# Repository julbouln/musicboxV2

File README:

New "La boîte à musique" firmware https://hackaday.io/project/6391-la-bote-musique

Using libopencm3 http://libopencm3.org/wiki/Main_Page drivers and atomthreads RTOS http://atomthreads.com/

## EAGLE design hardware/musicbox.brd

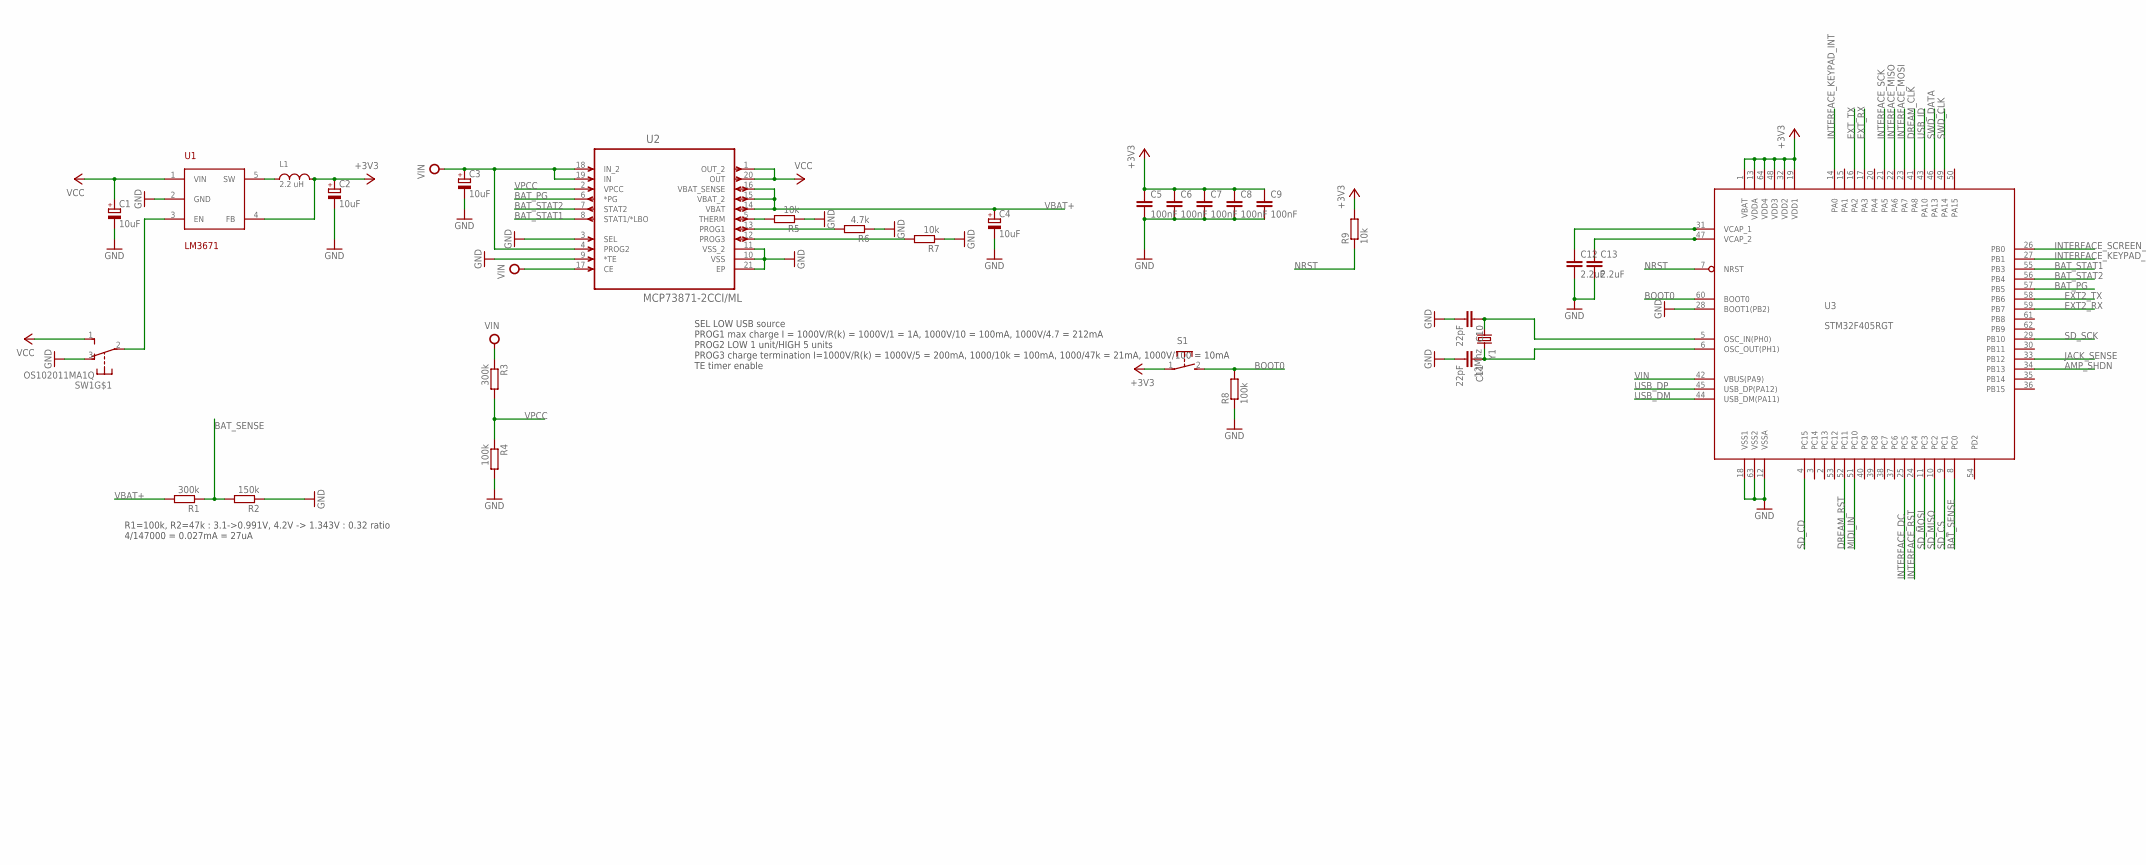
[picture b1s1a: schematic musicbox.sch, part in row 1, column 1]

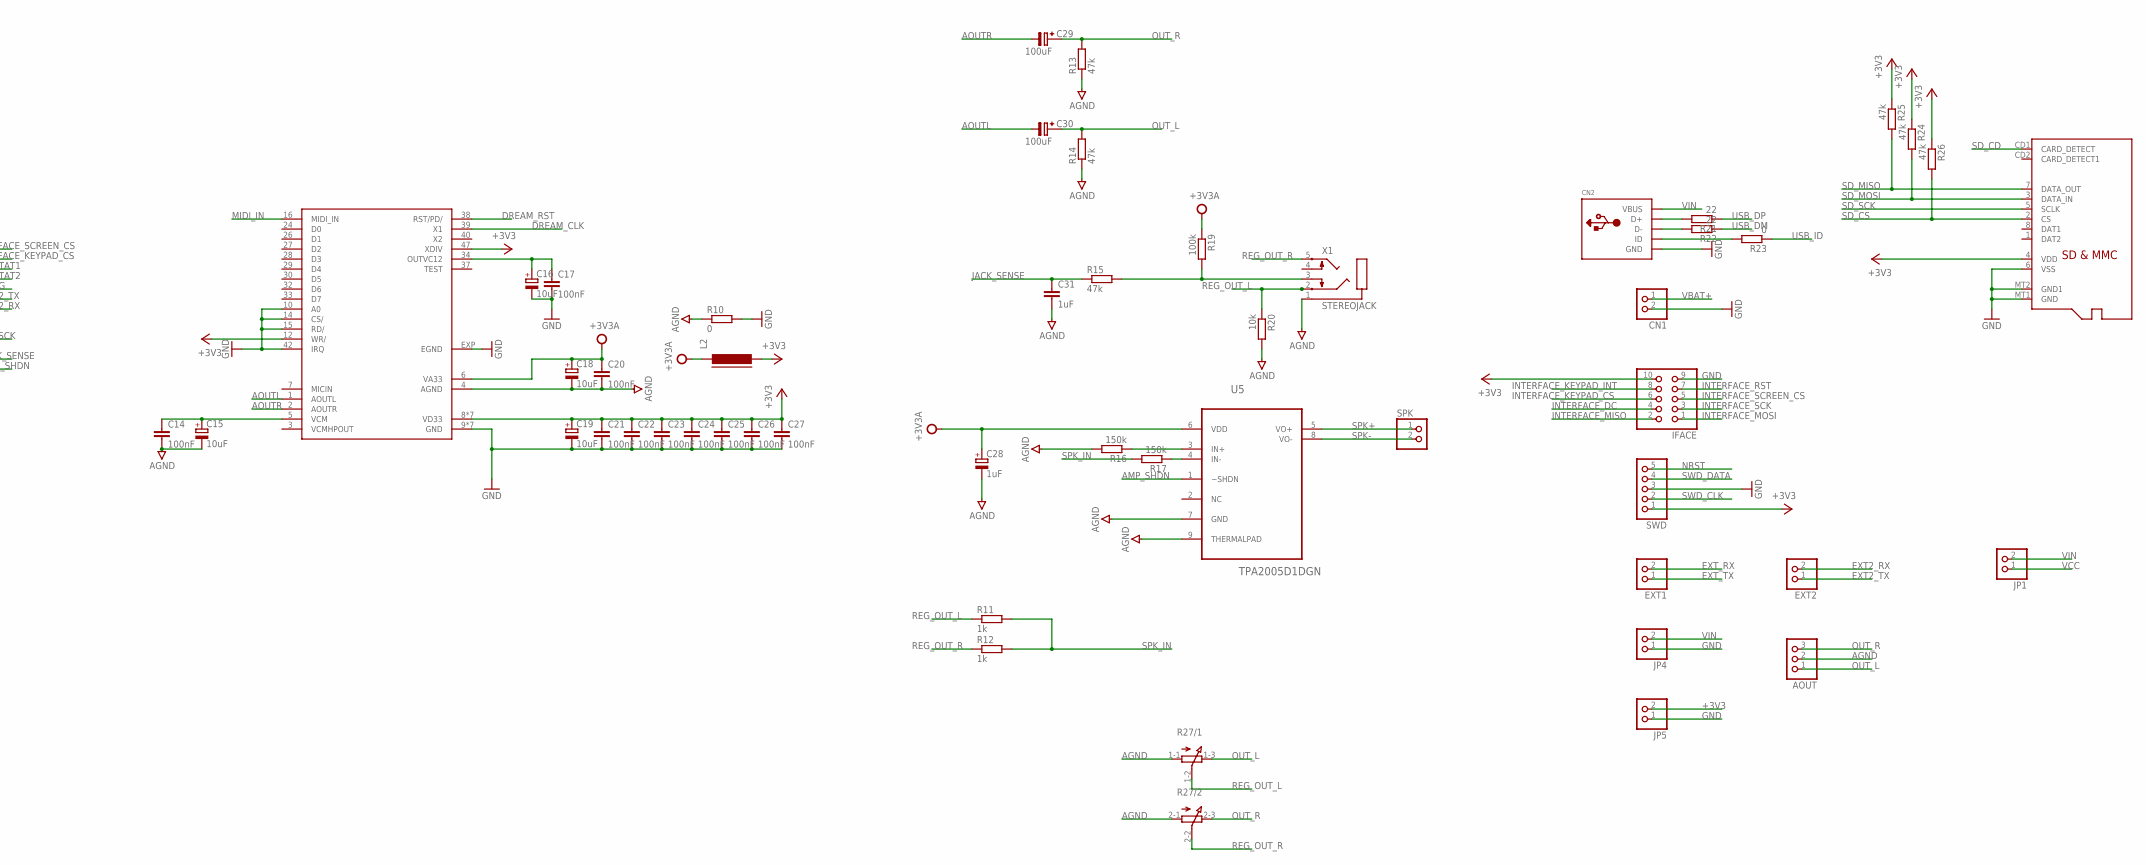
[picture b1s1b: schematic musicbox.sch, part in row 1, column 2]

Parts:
AOUT: HEADER-1X3ROUND; 1X03_ROUND
C1, C2, C3, C4, C15, C16, C18, C19: 10uF; A/3216-18R
C5, C6, C7, C8, C9, C14, C17, C20, C21, C22, C23, C24, C25, C26, C27: 100nF; C0603K
C10, C11: 22pF; C0603K
C12, C13: 2.2uF; C0603K
C28: 1uF; A/3216-18R
C29, C30: 100uF; SV-B
C31: 1uF; C0603K
CN1: JST_2PIN-THM; JST-PH-2-THM
CN2: USBMOLEX; USB-MINIB-THM-MOLEX
EXT1, EXT2: HEADER-1X2ROUND; 1X02_ROUND
IFACE: HEADER-2X5; 2X05
JP1, JP4, JP5: HEADER-1X2ROUND; 1X02_ROUND
L1: 2.2 uH; 4X4MM
L2: FERRITE-0603; FB603
R1, R3: 300k; R0603
R2, R16, R17: 150k; R0603
R4, R8, R19: 100k; R0603
R5, R7, R9, R20: 10k; R0603
R6: 4.7k; R0603
R10, R23: 0; R0603
R11, R12: 1k; R0603
R13, R14, R15, R24, R25, R26: 47k; R0603
R21, R22: 22; R0603
R27: 3RP/1610G
S1: 31-XX; B3F-31XX
SPK: HEADER-1X2ROUND; 1X02_ROUND
SW1: OS102011MA1Q
SWD: HEADER-1X5ROUND; 1X05_ROUND
U1: LM3671; SOT23-5
U2: MCP73871-2CCI/ML; QFN50P400X400X100-21N
U3: STM32F405RGT; LQFP64
U4: SAM2695; QFN48
U5: TPA2005D1DGN; SOP65P488X107-9N
U6: MICROSD
X1: STEREOJACK; STX3100
Y1: 12Mhz; CRYSTAL-TXC-7A

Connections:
+3V3: C2.+, C5.1, C6.1, C7.1, C8.1, C9.1, C19.+, C21.1, C22.1, C23.1, C24.1, C25.1, C26.1, C27.1, IFACE.10, JP5.2, L1.2, L2.2, R9.2, R24.1, R25.1, R26.1, S1.1, SWD.1, U1.4 (FB), U3.1 (VBAT), U3.13 (VDDA), U3.19 (VDD1), U3.32 (VDD2), U3.48 (VDD3), U3.64 (VDD4), U4.8 (VD33), U4.11 (VD33), U4.12 (WR/), U4.20 (VD33), U4.31 (VD33), U4.35 (VD33), U4.41 (VD33), U4.46 (VD33), U4.47 (XDIV), U6.4 (VDD)
+3V3A: C18.+, C20.1, C28.+, L2.1, R19.1, U4.6 (VA33), U5.6 (VDD)
AGND: AOUT.2, C14.2, C15.-, C18.-, C20.2, C28.-, C31.2, R10.1, R13.1, R14.1, R16.2, R20.2, R27.1-1 (A), R27.2-1 (A), U4.4 (AGND), U5.7 (GND), U5.9 (THERMALPAD), X1.1
AMP_SHDN: U3.34 (PB13), U5.1 (~SHDN)
AOUTL: C30.-, U4.1 (AOUTL)
AOUTR: C29.-, U4.2 (AOUTR)
BAT_PG: U2.6 (*PG), U3.57 (PB5)
BAT_SENSE: R1.1, R2.2, U3.8 (PC0)
BAT_STAT1: U2.8 (STAT1/*LBO), U3.55 (PB3)
BAT_STAT2: U2.7 (STAT2), U3.56 (PB4)
BOOT0: R8.2, S1.2 (S), U3.60 (BOOT0)
DREAM_CLK: U3.41 (PA8), U4.39 (X1)
DREAM_RST: U3.52 (PC11), U4.38 (RST/PD/)
EXT2_RX: EXT2.2, U3.59 (PB7)
EXT2_TX: EXT2.1, U3.58 (PB6)
EXT_RX: EXT1.2, U3.17 (PA3)
EXT_TX: EXT1.1, U3.16 (PA2)
GND: C1.-, C2.-, C3.-, C4.-, C5.2, C6.2, C7.2, C8.2, C9.2, C10.2, C11.2, C12.2, C13.2, C16.-, C17.2, C19.-, C21.2, C22.2, C23.2, C24.2, C25.2, C26.2, C27.2, CN1.2 (1), CN2.GND, IFACE.9, JP4.1, JP5.1, R2.1, R4.2, R5.1, R6.1, R7.1, R8.1, R10.2, SW1.3 (O), SWD.3, U1.2 (GND), U2.3 (SEL), U2.9 (*TE), U2.10 (VSS), U2.11 (VSS_2), U2.21 (EP), U3.12 (VSSA), U3.18 (VSS1), U3.28 (BOOT1(PB2)), U3.63 (VSS2), U4.9 (GND), U4.10 (A0), U4.13 (GND), U4.14 (CS/), U4.15 (RD/), U4.18 (GND), U4.25 (GND), U4.36 (GND), U4.42 (IRQ), U4.45 (GND), U4.48 (GND), U4.EXP (EGND), U6.6 (VSS), U6.MT1 (GND), U6.MT2 (GND1)
INTERFACE_DC: IFACE.4, U3.25 (PC5)
INTERFACE_KEYPAD_CS: IFACE.6, U3.27 (PB1)
INTERFACE_KEYPAD_INT: IFACE.8, U3.14 (PA0)
INTERFACE_MISO: IFACE.2, U3.22 (PA6)
INTERFACE_MOSI: IFACE.1, U3.23 (PA7)
INTERFACE_RST: IFACE.7, U3.24 (PC4)
INTERFACE_SCK: IFACE.3, U3.21 (PA5)
INTERFACE_SCREEN_CS: IFACE.5, U3.26 (PB0)
JACK_SENSE: C31.1, R15.1, U3.33 (PB12)
MIDI_IN: U3.51 (PC10), U4.16 (MIDI_IN)
unnamed: C12.1, U3.31 (VCAP_1)
unnamed: C11.1, U3.6 (OSC_OUT(PH1)), Y1.P$2 (2)
unnamed: C10.1, U3.5 (OSC_IN(PH0)), Y1.P$1 (1)
unnamed: C16.+, C17.1, U4.34 (OUTVC12)
unnamed: C14.1, C15.+, U4.5 (VCM)
unnamed: CN2.D+, R21.2
unnamed: C13.1, U3.47 (VCAP_2)
unnamed: L1.1, U1.5 (SW)
unnamed: CN2.D-, R22.2
unnamed: SW1.2, U1.3 (EN)
unnamed: CN2.ID, R23.2
unnamed: R5.2, U2.5 (THERM)
unnamed: R7.2, U2.12 (PROG3)
unnamed: R6.2, U2.13 (PROG1)
unnamed: R17.1, U5.4 (IN-)
unnamed: R16.1, U5.3 (IN+)
unnamed: R15.2, R19.2, X1.3
NRST: R9.1, SWD.5, U3.7 (NRST)
OUT_L: AOUT.1, C30.+, R14.2, R27.1-3 (E)
OUT_R: AOUT.3, C29.+, R13.2, R27.2-3 (E)
REG_OUT_L: R11.1, R20.1, R27.1-2 (S), X1.2
REG_OUT_R: R12.1, R27.2-2 (S), X1.5
SD_CD: U3.4 (PC15), U6.CD1 (CARD_DETECT)
SD_CS: R26.2, U3.9 (PC1), U6.2 (CS)
SD_MISO: R25.2, U3.10 (PC2), U6.7 (DATA_OUT)
SD_MOSI: R24.2, U3.11 (PC3), U6.3 (DATA_IN)
SD_SCK: U3.29 (PB10), U6.5 (SCLK)
SPK+: SPK.1, U5.5 (VO+)
SPK-: SPK.2, U5.8 (VO-)
SPK_IN: R11.2, R12.2, R17.2
SWD_CLK: SWD.2, U3.49 (PA14)
SWD_DATA: SWD.4, U3.46 (PA13)
USB_DM: R22.1, U3.44 (USB_DM(PA11))
USB_DP: R21.1, U3.45 (USB_DP(PA12))
USB_ID: R23.1, U3.43 (PA10)
VBAT+: C4.+, CN1.1 (2), R1.2, U2.14 (VBAT), U2.15 (VBAT_2), U2.16 (VBAT_SENSE)
VCC: C1.+, JP1.1, SW1.1 (S), U1.1 (VIN), U2.1 (OUT_2), U2.20 (OUT)
VIN: C3.+, CN2.VBUS, JP1.2, JP4.2, R3.1, U2.4 (PROG2), U2.17 (CE), U2.18 (IN_2), U2.19 (IN), U3.42 (VBUS(PA9))
VPCC: R3.2, R4.1, U2.2 (VPCC)

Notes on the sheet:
SEL LOW USB source PROG1 max charge I = 1000V/R(k) = 1000V/1 = 1A, 1000V/10 = 100mA, 1000V/4.7 = 212mA PROG2 LOW 1 unit/HIGH 5 units PROG3 charge termination I=1000V/R(k) = 1000V/5 = 200mA, 1000/10k = 100mA, 1000/47k = 21mA, 1000V/100 = 10mA TE timer enable
R1=100k, R2=47k : 3.1->0.991V, 4.2V -> 1.343V : 0.32 ratio 4/147000 = 0.027mA = 27uA

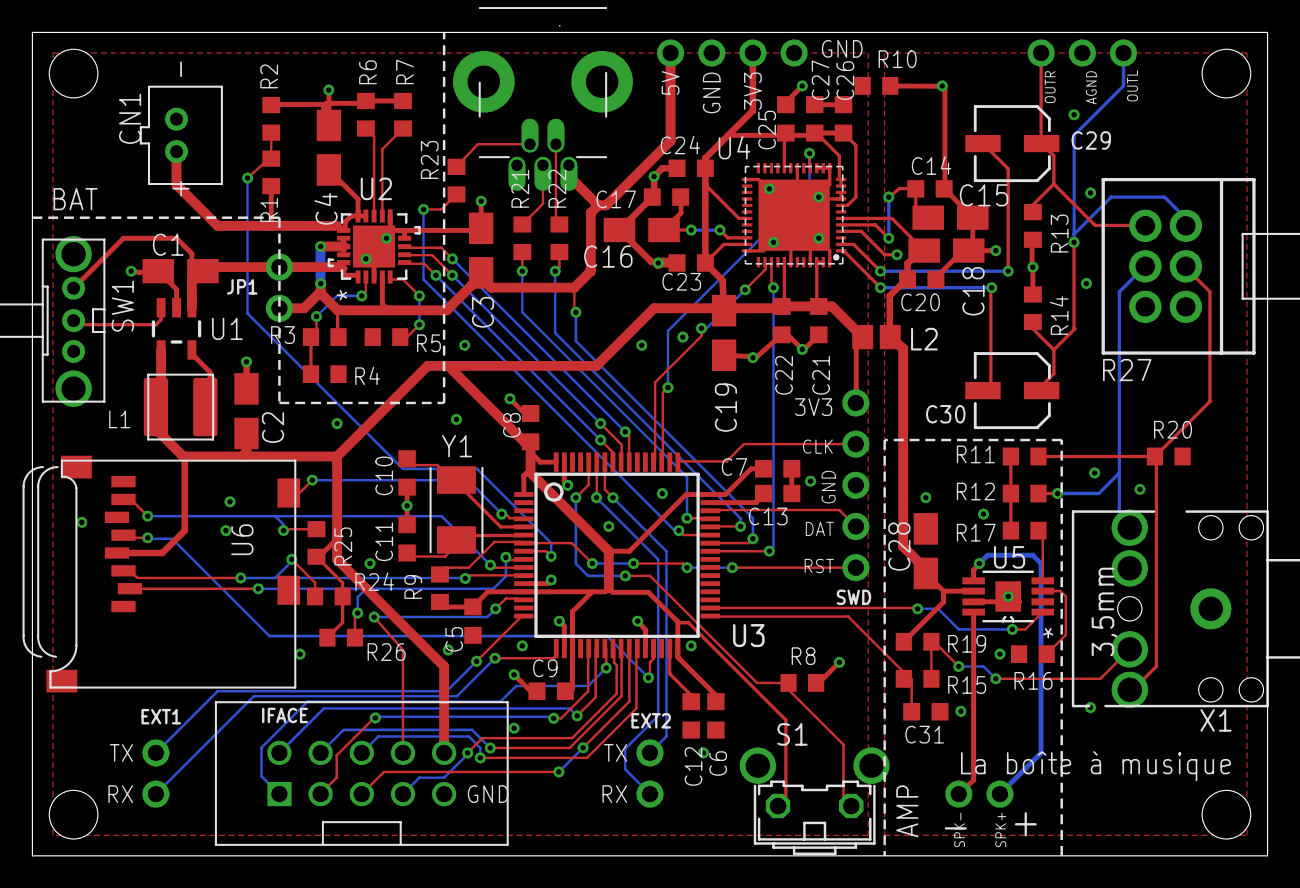
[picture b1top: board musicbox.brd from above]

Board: 2 copper layers, 76.2 x 50.8 mm, 81 parts (1 on the bottom side), 67 nets.

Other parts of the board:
U$1: PANDA

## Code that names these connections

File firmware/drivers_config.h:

#ifndef _DRIVERS_CONFIG_H
#define _DRIVERS_CONFIG_H

#define SAM2695_MIDI_IN_PORT GPIOC
#define SAM2695_MIDI_IN_PIN GPIO10
#define SAM2695_RESET_PORT GPIOC
#define SAM2695_RESET_PIN GPIO11

#define INTERFACE_SPI SPI1
#define INTERFACE_SPI_PORT GPIOA
#define INTERFACE_SPI_CLK_PIN GPIO5
#define INTERFACE_SPI_MISO_PIN GPIO6
#define INTERFACE_SPI_MOSI_PIN GPIO7

#define SSD1306_SPI INTERFACE_SPI
#define SSD1306_CS_PORT GPIOB
#define SSD1306_CS_PIN GPIO0
#define SSD1306_RST_PORT GPIOC
#define SSD1306_RST_PIN GPIO4
#define SSD1306_DC_PORT GPIOC
#define SSD1306_DC_PIN GPIO5

#define MCP23S08_SPI INTERFACE_SPI
#define MCP23S08_CS_PORT GPIOB
#define MCP23S08_CS_PIN GPIO1

#define BAT_SENSE_ADC ADC1

#define BAT_SENSE_PORT GPIOC
#define BAT_SENSE_PIN GPIO0
#define BAT_STAT_PORT GPIOB
#define BAT_STAT1_PORT BAT_STAT_PORT
#define BAT_STAT1_PIN GPIO3
#define BAT_STAT2_PORT BAT_STAT_PORT
#define BAT_STAT2_PIN GPIO4
#define BAT_PG_PORT BAT_STAT_PORT
#define BAT_PG_PORT GPIO5

#define JACK_SENSE_PORT GPIOB
#define JACK_SENSE_PIN GPIO12
#define AMP_SHDN_PORT GPIOB
#define AMP_SHDN_PIN GPIO13

#endif

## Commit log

2016-02-20 ccgmusic submodule

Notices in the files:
parts and their libraries:
SparkFun-FreqCtrl: Licensing: Creative Commons ShareAlike 4.0 International - https://creativecommons.org/licenses/by-sa/4.0
microbuilder: This work is placed in the public domain, and may be freely used for commercial and non-commercial work with the following conditions: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
